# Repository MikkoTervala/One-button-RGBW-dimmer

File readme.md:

This dimmer was built for a car. It uses a single button to cycle between colors. 
Other features include:

- 6 RGBW outputs.
- Individually fused channels, 4 polyfuses for each output, 24 fuses in total.
- OTA update over wifi, starts to OTA mode by holding button while starting car.

Microcontroller is the ESP8266 and code is written in arduino. Kicad is used for the PCB design.

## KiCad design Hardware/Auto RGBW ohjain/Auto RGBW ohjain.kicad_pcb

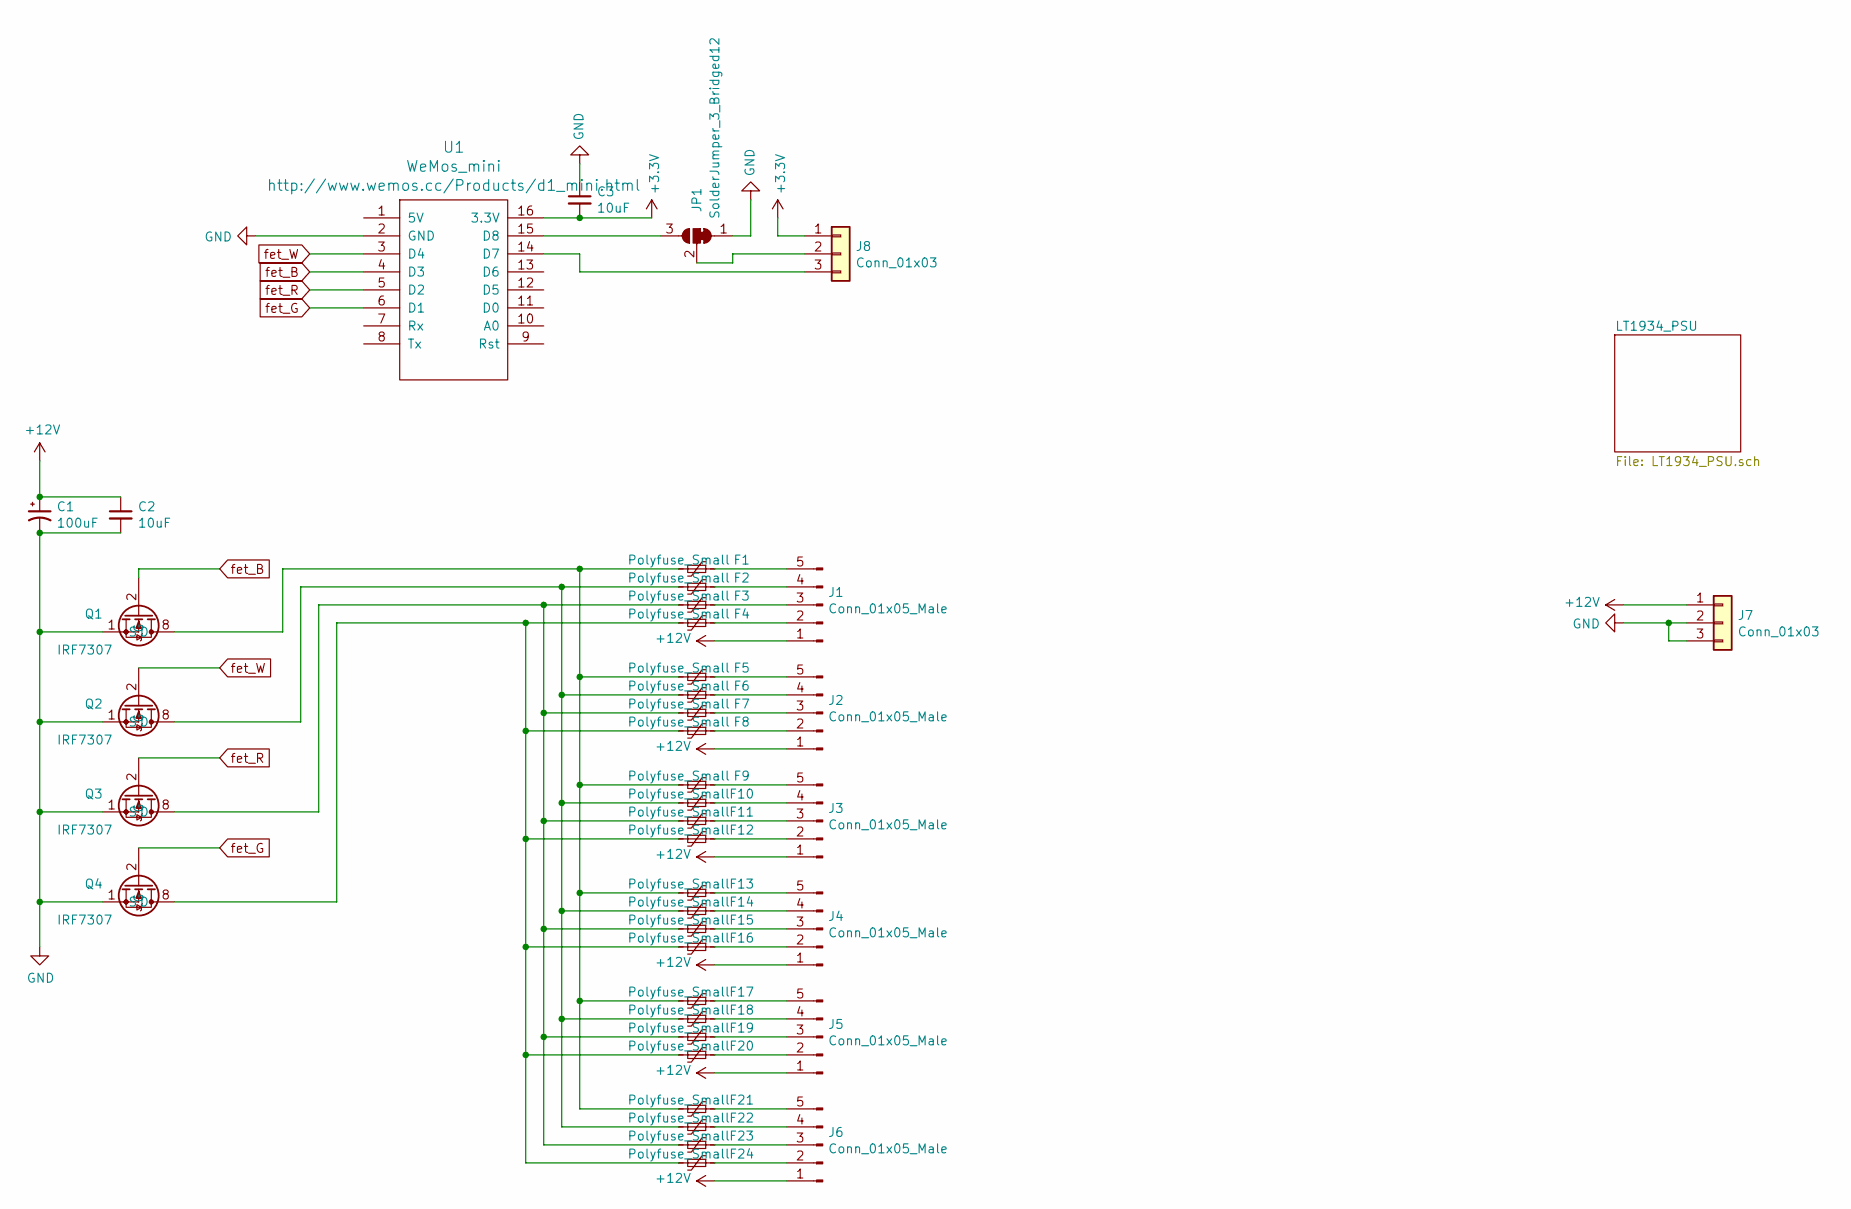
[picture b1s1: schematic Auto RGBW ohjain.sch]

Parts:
C1: 100uF; CP_Radial_D6.3mm_P2.50mm
C2, C3: 10uF; C_1210_3225Metric
F1, F2, F3, F4, F5, F6, F7, F8, F9, F10, F11, F12, F13, F14, F15, F16, F17, F18, F19, F20, F21, F22, F23, F24: Polyfuse_Small; Fuse_1206_3216Metric; Manufacture Part Number 1206L035/16YR; LCSC Part Number C126817
J1, J2, J3, J4, J5, J6: Conn_01x05_Male; JST_XH_B05B-XH-A_1x05_P2.50mm_Vertical
J7, J8: Conn_01x03; WJ250B-3.50-3P
JP1: SolderJumper_3_Bridged12; SolderJumper-3_P1.3mm_Bridged12_RoundedPad1.0x1.5mm
Q1, Q2, Q3, Q4: IRF7307; SO-8_5.3x6.2mm_P1.27mm
U1: WeMos_mini; D1_mini_board

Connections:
+3V3: C3.2, J8.1, U1.16 (3.3V); also elsewhere on the board
+12V: C1.1, C2.1, J1.1, J2.1, J3.1, J4.1, J5.1, J6.1, J7.1; also elsewhere on the board
GND: C1.2, C2.2, C3.1, J7.2, J7.3, JP1.1 (A), Q1.1 (S), Q2.1 (S), Q3.1 (S), Q4.1 (S), U1.2 (GND); also elsewhere on the board
unnamed: F1.1, J1.5
unnamed: F1.2, F5.2, F9.2, F13.2, F17.2, F21.2, Q1.7 (D), Q1.8 (D)
unnamed: F2.1, J1.4
unnamed: F3.1, J1.3
unnamed: F4.1, J1.2
unnamed: F5.1, J2.5
unnamed: F6.1, J2.4
unnamed: F7.1, J2.3
unnamed: F8.1, J2.2
unnamed: F9.1, J3.5
unnamed: F10.1, J3.4
unnamed: F2.2, F6.2, F10.2, F14.2, F18.2, F22.2, Q2.7 (D), Q2.8 (D)
unnamed: F11.1, J3.3
unnamed: F3.2, F7.2, F11.2, F15.2, F19.2, F23.2, Q3.7 (D), Q3.8 (D)
unnamed: F12.1, J3.2
unnamed: F4.2, F8.2, F12.2, F16.2, F20.2, F24.2, Q4.7 (D), Q4.8 (D)
unnamed: F13.1, J4.5
unnamed: F14.1, J4.4
unnamed: F15.1, J4.3
unnamed: F16.1, J4.2
unnamed: F17.1, J5.5
unnamed: F18.1, J5.4
unnamed: F19.1, J5.3
unnamed: F20.1, J5.2
unnamed: F21.1, J6.5
unnamed: F22.1, J6.4
unnamed: F23.1, J6.3
unnamed: F24.1, J6.2
unnamed: J8.2, JP1.2 (C)
unnamed: J8.3, U1.14 (D7)
unnamed: JP1.3 (B), U1.15 (D8)
fet_B: Q1.2 (G), U1.4 (D3)
fet_G: Q4.2 (G), U1.6 (D1)
fet_R: Q3.2 (G), U1.5 (D2)
fet_W: Q2.2 (G), U1.3 (D4)

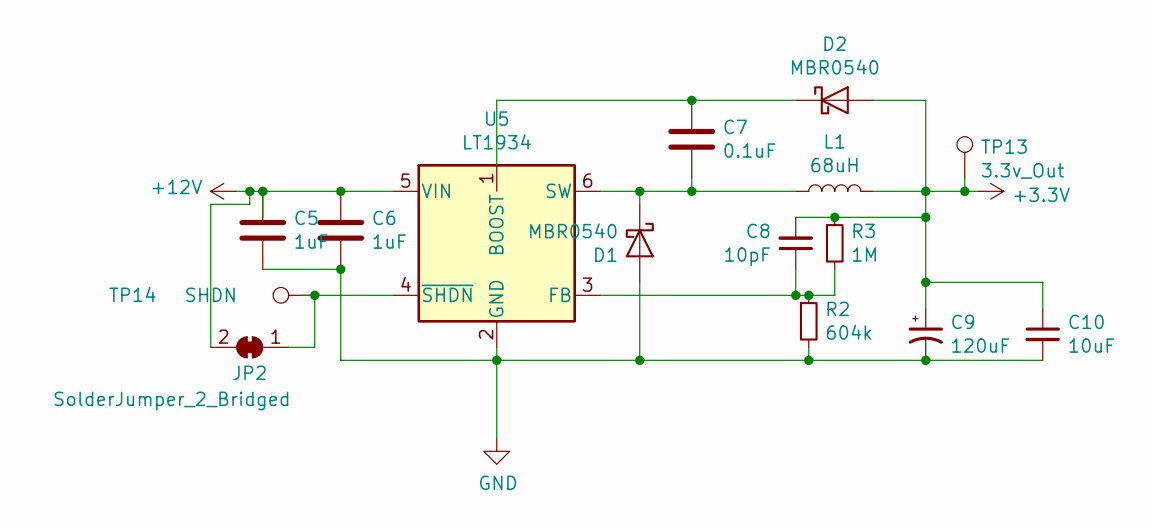
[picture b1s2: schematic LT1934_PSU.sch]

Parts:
C5, C6: 1uF; C_1206_3216Metric
C7: 0.1uF; C_0805_2012Metric; Manufacture Part Number GRM2165C2A101JA01D; LCSC Part Number C97903
C8: 10pF; C_0805_2012Metric
C9: 120uF; CP_Radial_D6.3mm_P2.50mm
C10: 10uF; C_1210_3225Metric
D1, D2: MBR0540; D_SOD-123; Manufacture Part Number MBR0540L-CA2-R; LCSC Part Number C89706
JP2: SolderJumper_2_Bridged; SolderJumper-2_P1.3mm_Bridged_RoundedPad1.0x1.5mm
L1: 68uH; L_SUMIDA_CDRH5D28
R2: 604k; R_0805_2012Metric; Manufacture Part Number 0805W8F6043T5E; LCSC Part Number C17776
R3: 1M; R_0805_2012Metric; Manufacture Part Number 0805W8F1004T5E; LCSC Part Number C17514
TP13: 3.3v_Out; TestPoint_Loop_D2.50mm_Drill1.0mm
TP14: SHDN; TestPoint_Pad_D1.0mm
U5: LT1934; SOT-23-6

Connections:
+3V3: C8.2, C9.1, C10.1, D2.2 (A), L1.2, R3.1, TP13.1; also elsewhere on the board
+12V: C5.2, C6.2, JP2.2 (B), U5.5 (VIN); also elsewhere on the board
GND: C5.1, C6.1, C9.2, C10.2, D1.2 (A), R2.2, U5.2 (GND); also elsewhere on the board
unnamed: C7.1, D2.1 (K), U5.1 (BOOST)
unnamed: C7.2, D1.1 (K), L1.1, U5.6 (SW)
unnamed: C8.1, R2.1, R3.2, U5.3 (FB)
unnamed: JP2.1 (A), TP14.1, U5.4 (~SHDN)

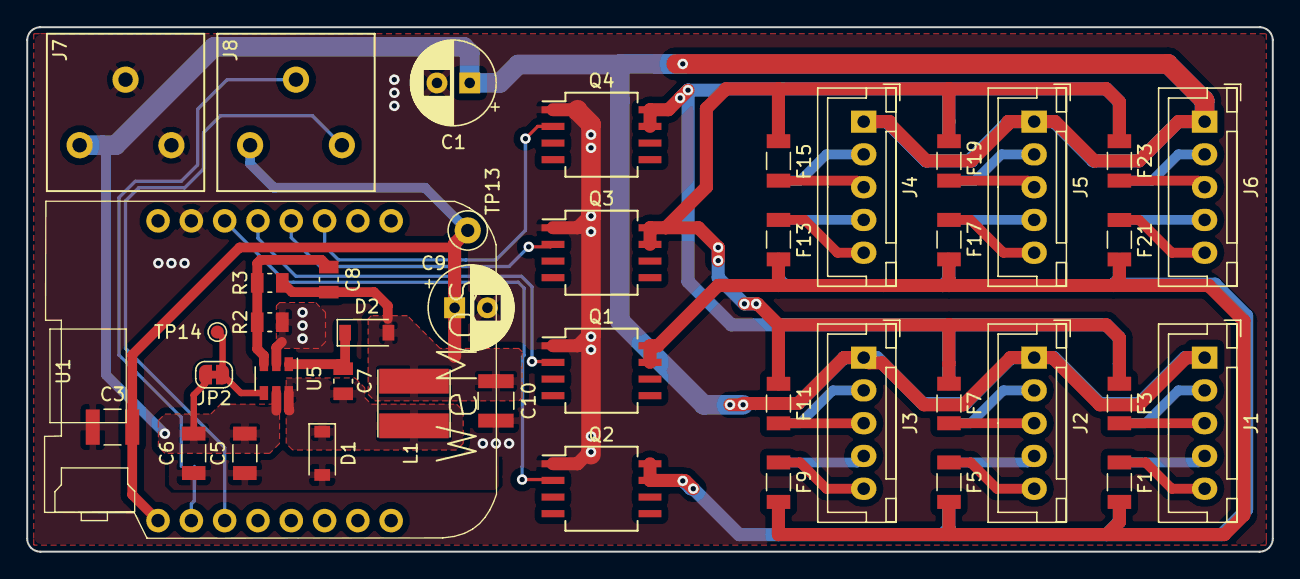
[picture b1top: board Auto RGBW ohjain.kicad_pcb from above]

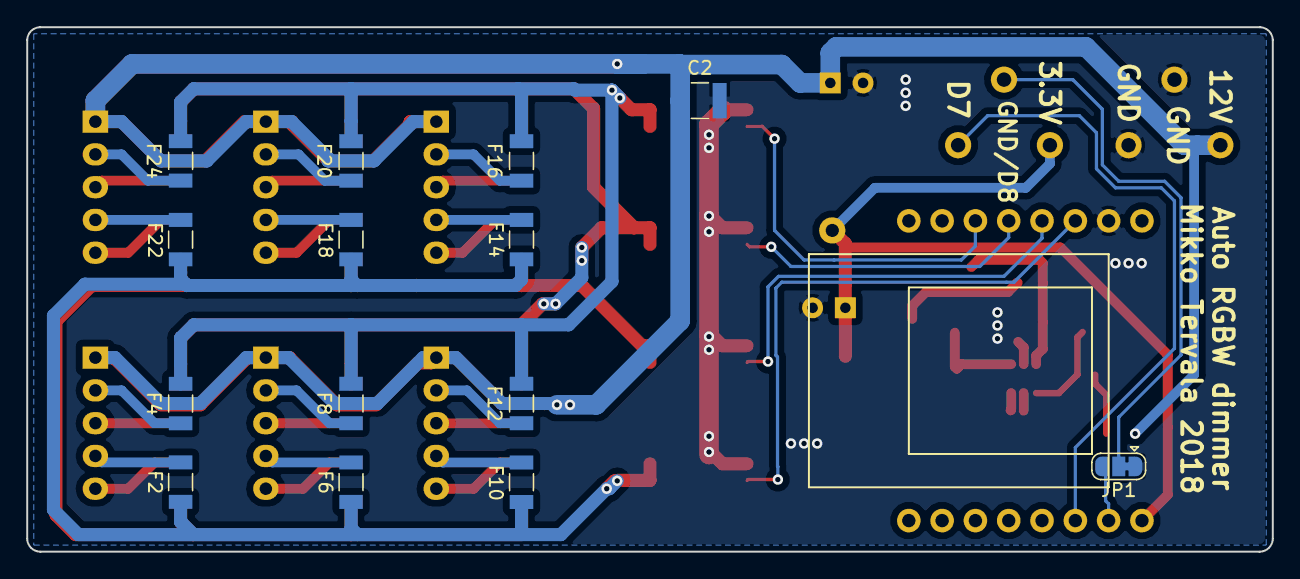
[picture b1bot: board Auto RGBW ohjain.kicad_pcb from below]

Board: 2 copper layers, 95.0 x 40.0 mm, 56 parts (14 on the bottom side), 42 nets.

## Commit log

2018-07-07 First release
2018-07-07 Updated software folder
2018-07-07 Add lines and picture
